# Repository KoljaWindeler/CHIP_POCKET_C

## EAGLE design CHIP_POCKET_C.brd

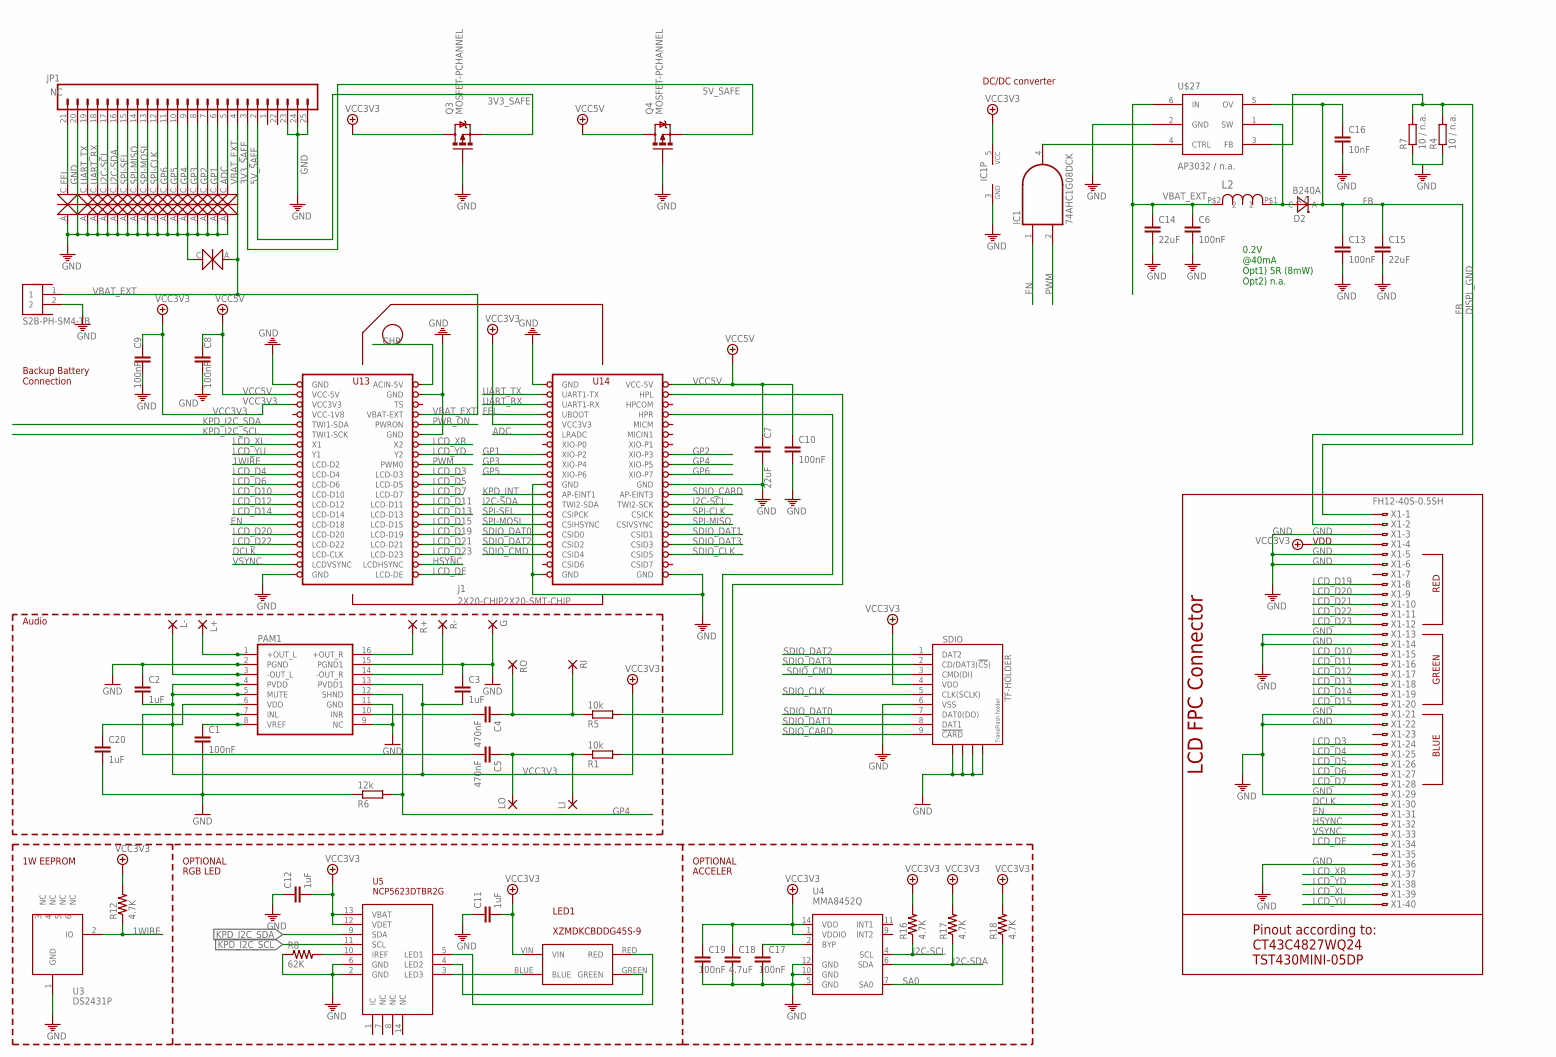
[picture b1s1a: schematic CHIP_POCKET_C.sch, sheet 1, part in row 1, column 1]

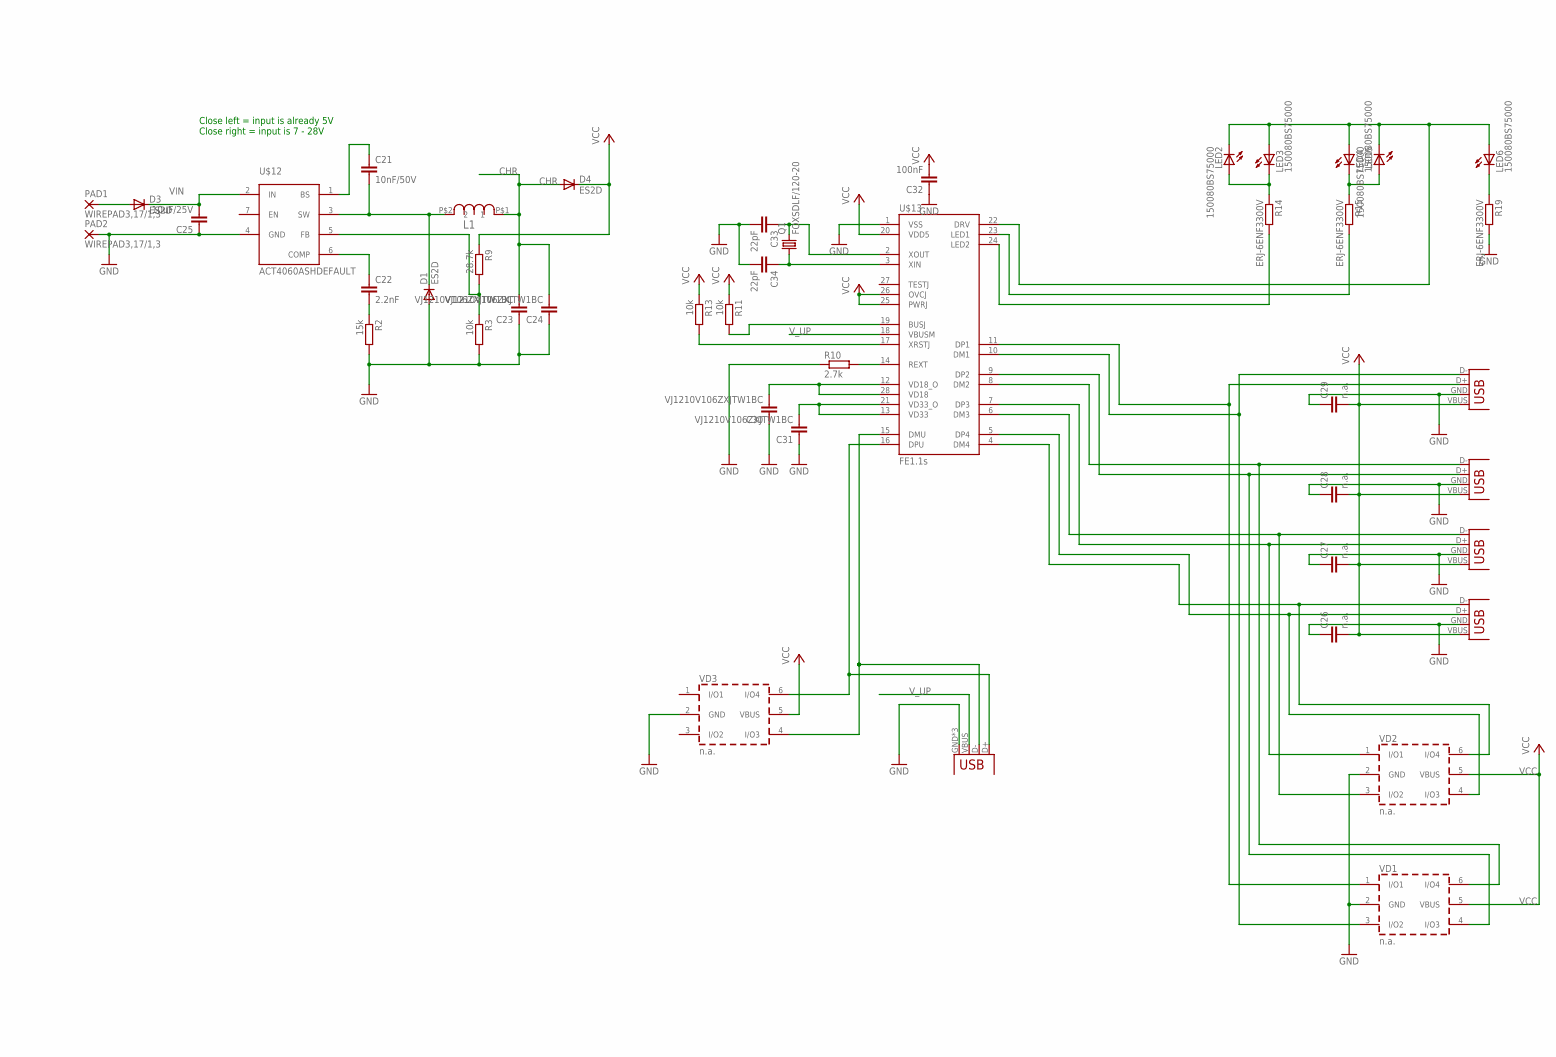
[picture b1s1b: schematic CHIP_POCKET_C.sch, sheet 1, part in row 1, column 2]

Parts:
C1, C6, C13, C32: 100nF; C0805
C2, C3, C20: 1uF; C0805
C4, C5: 470nF; C0805
C7, C14, C15: 22uF; C1206
C8, C9, C10, C17, C19: 100nF; C0402
C11, C12: 1uF; C0402
C16: 10nF; C0805
C18: 4.7uF; C0402
C21: 10nF/50V; C0805
C22: 2.2nF; C0805
C23, C24, C30, C31: VJ1210V106ZXJTW1BC; C1210
C25: 10uF/25V; C1210
C26, C27, C28, C29: n.a.; C1210
C33, C34: 22pF; C0805
D1, D3, D4: ES2D; SMB
D2: B240A; DO-214AC
DATA_USB: USBUSB-MICROB-SMT-DIP; USB-MICROB-SMT-DIP
ESD1, ESD2, ESD3, ESD4, ESD5, ESD6, ESD7, ESD8, ESD9, ESD10, ESD11, ESD12, ESD13, ESD14, ESD15, ESD16, ESD17: ESD5Z2.5T1G; SOD523
G: 1,6/0,8
IC1: 74AHC1G08DCK; SC70-5
J1: 2X20-CHIP2X20-SMT-CHIP; 2XAWHW40_G_SMD_R
J3: S2B-PH-SM4-TB
JP1: NC; 1X20_LOCK_LONGPADS
L1, L2: SRN6045-100M; SRN6045
L+: 1,6/0,8
L-: 1,6/0,8
LED1: XZMDKCBDDG45S-9
LED2, LED3, LED4, LED5, LED6: 150080BS75000; CHIP-LED0805
LI: 1,6/0,8
LO: 1,6/0,8
PAD1, PAD2: WIREPAD3,17/1,3; 3,17/1,3
PAM1: PAM8403; SOP-16
Q1: FOXSDLF/120-20; SM49
Q3, Q4: MOSFET-PCHANNEL; SOT23-3
R1, R3, R5, R11, R13: 10k; R0805
R2: 15k; R0805
R4, R7: 10 / n.a.; M0805
R6: 12k; R0805
R8: 62K; R0402
R9: 28.7k; R0805
R10: 2.7k; R0805
R12, R16, R17, R18: 4.7K; R0402
R14, R15, R19: ERJ-6ENF3300V; R0805
R+: 1,6/0,8
R-: 1,6/0,8
RI: 1,6/0,8
RO: 1,6/0,8
SDIO: TF-HOLDER; TF-PULL
U3: DS2431P; TSOC6
U4: MMA8452Q; QFN-16_0.5MM
U5: NCP5623DTBR2G; TSSOP14
U$12: ACT4060ASHDEFAULT; SOP-8
U$13: FE1.1S; FE1.1S_SSOP-28
U$27: AP3032 / n.a.; SOT23-6
VD1, VD2, VD3: n.a.; SOT-23-6L
X1: FH12-40S-0.5SH
X2, X3, X4, X5: USB-A-HU

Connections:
1WIRE: J1.LCD-D2, R12.1, U3.2 (IO)
3V3_SAFE: JP1.2, Q3.2 (S)
5V_SAFE: JP1.3, Q4.2 (S)
ADC: ESD16.C, J1.LRADC, JP1.5
AUDIO_L: J1.HPL, R1.2
AUDIO_R: J1.HPR, R5.2
CHR: C23.2, C24.2, D4.A, J1.CHG-IN (ACIN-5V), L1.P$1 (1)
DCLK: J1.LCD-CLK, X1.30
DISPL_GND: R4.2, R7.2, U$27.3 (FB), X1.1
DM1: U$13.10 (DM1), VD1.3 (I/O2), X5.D- (D+)
DM2: U$13.8 (DM2), VD1.6 (I/O4), X4.D- (D+)
DM3: U$13.6 (DM3), VD2.3 (I/O2), X3.D- (D+)
DM4: U$13.4 (DM4), VD2.6 (I/O4), X2.D- (D+)
DMU: DATA_USB.D-, U$13.15 (DMU), VD3.4 (I/O3)
DP1: U$13.11 (DP1), VD1.1 (I/O1), X5.D+ (D-)
DP2: U$13.9 (DP2), VD1.4 (I/O3), X4.D+ (D-)
DP3: U$13.7 (DP3), VD2.1 (I/O1), X3.D+ (D-)
DP4: U$13.5 (DP4), VD2.4 (I/O3), X2.D+ (D-)
DPU: DATA_USB.D+, U$13.16 (DPU), VD3.6 (I/O4)
EN: IC1.1 (I0), J1.LCD-D18, X1.31
FB: C13.1, C15.1, C16.1, D2.C, U$27.5 (OV), X1.2
FEL: ESD1.C, J1.FEL (UBOOT), JP1.21
GND: C1.2, C2.1, C3.1, C6.2, C7.2, C8.2, C9.2, C10.2, C11.1, C12.1, C13.2, C14.2, C15.2, C16.2, C17.2, C18.2, C19.2, C20.2, C23.1, C24.1, C25.1, C26.1, C27.1, C28.1, C29.1, C30.1, C31.1, C32.1, C33.2, C34.2, D1.A, DATA_USB.GND, DATA_USB.MT1 (GND), DATA_USB.MT2 (GND), ESD1.A, ESD2.A, ESD3.A, ESD4.A, ESD5.A, ESD6.A, ESD7.A, ESD8.A, ESD9.A, ESD10.A, ESD11.A, ESD12.A, ESD13.A, ESD14.A, ESD15.A, ESD16.A, ESD17.C, G.1, IC1.3 (GND), J1.GND@1 (GND), J1.GND@2 (GND), J1.GND@3 (GND), J1.GND@4 (GND), J1.GND@5 (GND), J1.GND@6 (GND), J1.GND@7 (GND), J1.GND@8 (GND), J1.GND@10 (GND), J3.2, JP1.20, JP1.23, JP1.24, JP1.25, PAD2.1, PAM1.2 (PGND), PAM1.9 (NC), PAM1.11 (GND), PAM1.15 (PGND1), Q3.1 (G), Q4.1 (G), R3.2, R4.1, R6.1, R7.1, R8.1, R10.1, R19.2, SDIO.6 (VSS), SDIO.S1, SDIO.S2, SDIO.S3, SDIO.S4, U3.1 (GND), U4.5 (GND), U4.10 (GND), U4.12 (GND), U5.2 (GND), U5.6 (GND), U$12.4 (GND), U$13.1 (VSS), U$27.2 (GND), VD1.2 (GND), VD2.2 (GND), VD3.2 (GND), X1.3, X1.5, X1.6, X1.13, X1.14, X1.21, X1.22, X1.29, X1.36, X2.GND (VBUS), X3.GND (VBUS), X4.GND (VBUS), X5.GND (VBUS)
GP1: ESD15.C, J1.XIO-P2, JP1.6
GP2: ESD14.C, J1.XIO-P3, JP1.7
GP3: ESD13.C, J1.XIO-P4, JP1.8
GP4: ESD12.C, J1.XIO-P5, JP1.9, PAM1.12 (SHND), R6.2
GP5: ESD11.C, J1.XIO-P6, JP1.10
GP6: ESD10.C, J1.XIO-P7, JP1.11
HSYNC: J1.LCD-HSYNC (LCDHSYNC), X1.32
I2C-SCL: ESD4.C, J1.TWI2-SCK, JP1.17, R16.1, U4.4 (SCL)
I2C-SDA: ESD5.C, J1.TWI2-SDA, JP1.16, R17.1, U4.6 (SDA)
INL: C5.2, PAM1.7 (INL)
INR: C4.2, PAM1.10 (INR)
KPD_I2C_SCL: J1.TWI1-SCK, U5.11 (SCL)
KPD_I2C_SDA: J1.TWI1-SDA, U5.9 (SDA)
KPD_INT: J1.AP-EINT1
L+OUT: L+.1, PAM1.1 (+OUT_L)
L-OUT: L-.1, PAM1.3 (-OUT_L)
LCD_D3: J1.LCD-D3, X1.24
LCD_D4: J1.LCD-D4, X1.25
LCD_D5: J1.LCD-D5, X1.26
LCD_D6: J1.LCD-D6, X1.27
LCD_D7: J1.LCD-D7, X1.28
LCD_D10: J1.LCD-D10, X1.15
LCD_D11: J1.LCD-D11, X1.16
LCD_D12: J1.LCD-D12, X1.17
LCD_D13: J1.LCD-D13, X1.18
LCD_D14: J1.LCD-D14, X1.19
LCD_D15: J1.LCD-D15, X1.20
LCD_D19: J1.LCD-D19, X1.8
LCD_D20: J1.LCD-D20, X1.9
LCD_D21: J1.LCD-D21, X1.10
LCD_D22: J1.LCD-D22, X1.11
LCD_D23: J1.LCD-D23, X1.12
LCD_DE: J1.LCD-DE, X1.34
LCD_XL: J1.X1, X1.39
LCD_XR: J1.X2, X1.37
LCD_YD: J1.Y2, X1.38
LCD_YU: J1.Y1, X1.40
unnamed: C17.1, U4.2 (BYP)
unnamed: LED1.GREEN, U5.4 (LED2)
unnamed: LED1.RED, U5.5 (LED1)
unnamed: R8.2, U5.10 (IREF)
unnamed: IC1.4 (O), U$27.4 (CTRL)
unnamed: C1.1, PAM1.8 (VREF)
unnamed: C5.1, LI.1, LO.1, R1.1
unnamed: C4.1, R5.1, RI.1, RO.1
unnamed: D3.A, PAD1.1
unnamed: C21.2, D1.C, L1.P$2 (2), U$12.3 (SW)
unnamed: C21.1, U$12.1 (BS)
unnamed: C22.2, R2.1
unnamed: C22.1, U$12.6 (COMP)
unnamed: R3.1, R9.2, U$12.5 (FB)
unnamed: C31.2, U$13.13 (VD33), U$13.21 (VD33_O)
unnamed: C30.2, U$13.12 (VD18_O), U$13.28 (VD18)
unnamed: R10.2, U$13.14 (REXT)
unnamed: R13.2, U$13.17 (XRSTJ)
unnamed: R11.2, U$13.19 (BUSJ)
unnamed: C33.1, Q1.2, U$13.2 (XOUT)
unnamed: C34.1, Q1.1, U$13.3 (XIN)
unnamed: LED6.C, R19.1
unnamed: LED4.C, LED5.A, R15.1
unnamed: LED2.A, LED3.C, R14.1
unnamed: LED2.C, LED3.A, LED4.A, LED5.C, LED6.A, U$13.22 (DRV)
unnamed: R14.2, U$13.24 (LED2)
unnamed: R15.2, U$13.23 (LED1)
unnamed: LED1.BLUE, U5.3 (LED3)
PWM: IC1.2 (I1), J1.PWM0
PWR_ON: J1.PWRON
R+OUT: PAM1.16 (+OUT_R), R+.1
R-OUT: PAM1.14 (-OUT_R), R-.1
SA0: R18.1, U4.7 (SA0)
SDIO_CARD: J1.AP-EINT3, SDIO.9 (!CARD)
SDIO_CLK: J1.CSID5, SDIO.5 (CLK(SCLK))
SDIO_CMD: J1.CISD4 (CSID4), SDIO.3 (CMD(DI))
SDIO_DAT0: J1.CSID0, SDIO.7 (DAT0(DO))
SDIO_DAT1: J1.CSID1, SDIO.8 (DAT1)
SDIO_DAT2: J1.CSID2, SDIO.1 (DAT2)
SDIO_DAT3: J1.CSID3, SDIO.2 (CD/DAT3(!CS!))
SPI-CLK: ESD9.C, J1.CSICK, JP1.12
SPI-MISO: ESD7.C, J1.CSIVSYNC, JP1.14
SPI-MOSI: ESD8.C, J1.CSIHYSYNC (CSIHSYNC), JP1.13
SPI-SEL: ESD6.C, J1.CSPICK (CSIPCK), JP1.15
UART_RX: ESD3.C, J1.UART1-RX, JP1.18
UART_TX: ESD2.C, J1.UART1-TX, JP1.19
VBAT_EXT: C6.1, C14.1, ESD17.A, J1.BAT (VBAT-EXT), J3.1, JP1.4, L2.P$2 (2), U$27.6 (IN)
VCC: C26.2, C27.2, C28.2, C29.2, C32.2, D4.C, R9.1, R11.1, R13.1, U$13.20 (VDD5), U$13.25 (PWRJ), U$13.26 (OVCJ), VD1.5 (VBUS), VD2.5 (VBUS), VD3.5 (VBUS), X2.VBUS (GND), X3.VBUS (GND), X4.VBUS (GND), X5.VBUS (GND)
VCC3V3: C2.2, C3.2, C9.1, C11.2, C12.2, C18.1, C19.1, C20.1, IC1.5 (VCC), J1.VCC3V3@1 (VCC3V3), J1.VCC3V3@2 (VCC3V3), LED1.VIN, PAM1.4 (PVDD), PAM1.5 (MUTE), PAM1.6 (VDD), PAM1.13 (PVDD1), Q3.3 (D), R12.2, R16.2, R17.2, R18.2, SDIO.4 (VDD), U4.1 (VDDIO), U4.14 (VDD), U5.12 (VDET), U5.13 (VBAT), X1.4
VCC5V: C7.1, C8.1, C10.1, J1.VCC-5V@1 (VCC-5V), J1.VCC-5V@2 (VCC-5V), Q4.3 (D)
VCC-1V8: J1.VCC1V8 (VCC-1V8)
VIN: C25.2, D3.C, U$12.2 (IN)
VREG_OUTPUT1: D2.A, L2.P$1 (1), U$27.1 (SW)
VSYNC: J1.LCD-VSYNC (LCDVSYNC), X1.33
V_UP: DATA_USB.VBUS, U$13.18 (VBUSM)

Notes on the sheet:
LCD FPC Connector
VDD
RED
GREEN
BLUE
Pinout according to: CT43C4827WQ24 TST430MINI-05DP
Backup Battery Connection
1W EEPROM
OPTIONAL
RGB LED
ACCELER
DC/DC converter
0.2V @40mA Opt1) 5R (8mW) Opt2) n.a.
Audio
Close left = input is already 5V Close right = input is 7 - 28V

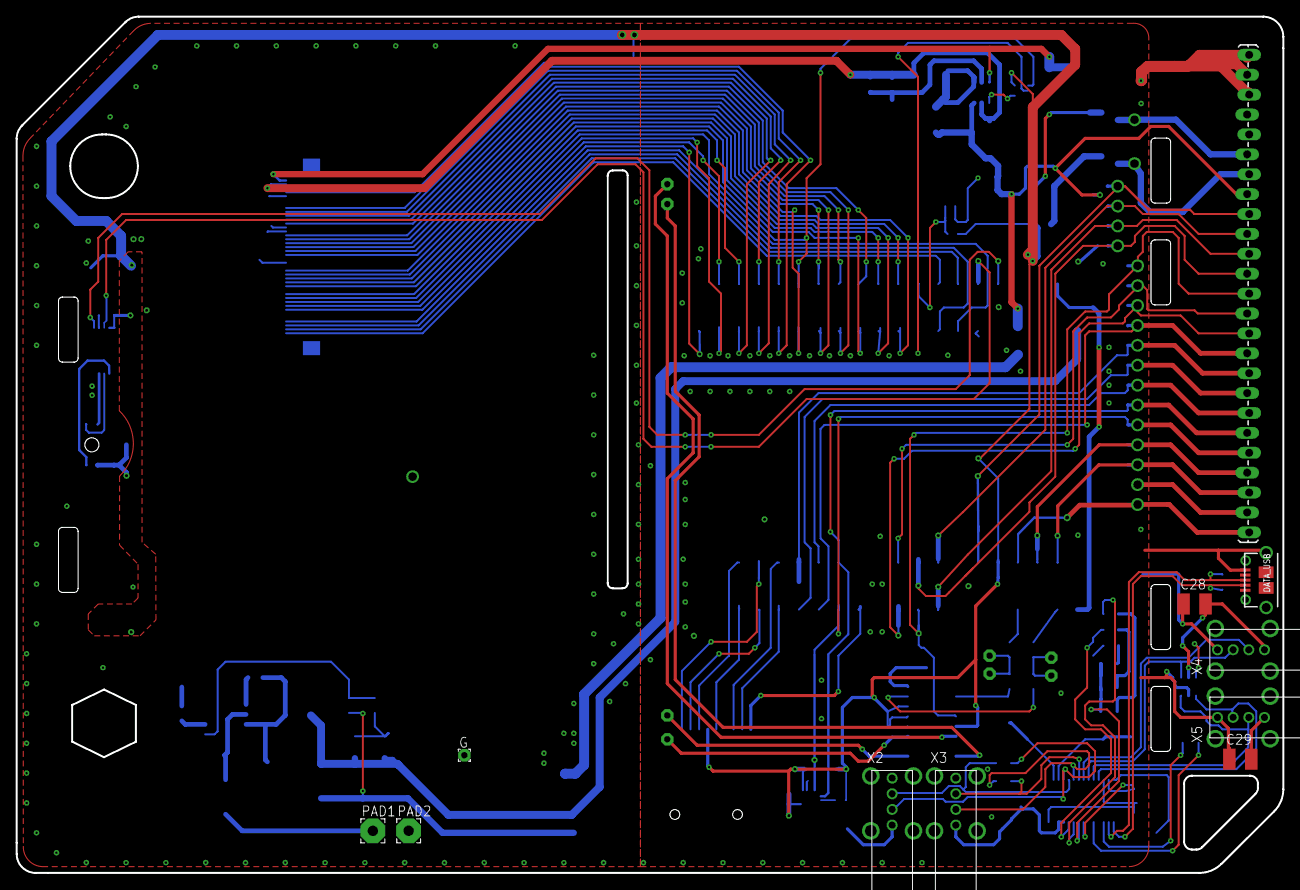
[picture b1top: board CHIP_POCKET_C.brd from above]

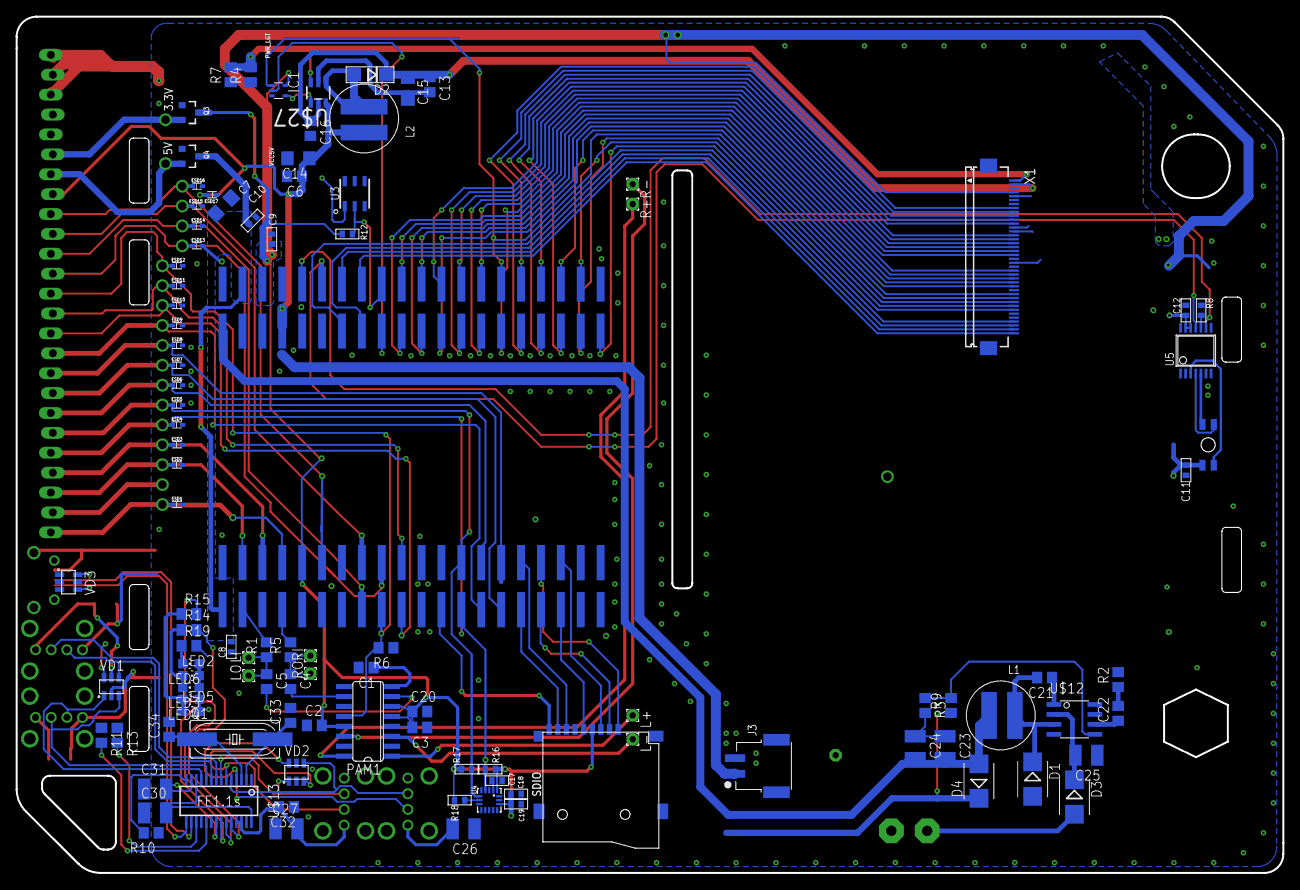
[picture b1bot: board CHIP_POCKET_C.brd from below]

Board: 4 copper layers, 161.7 x 109.3 mm, 117 parts (105 on the bottom side), 112 nets.

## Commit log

2016-12-22 :tada: Added .gitattributes & .gitignore files
2016-12-22 init
2016-12-23 added hub
